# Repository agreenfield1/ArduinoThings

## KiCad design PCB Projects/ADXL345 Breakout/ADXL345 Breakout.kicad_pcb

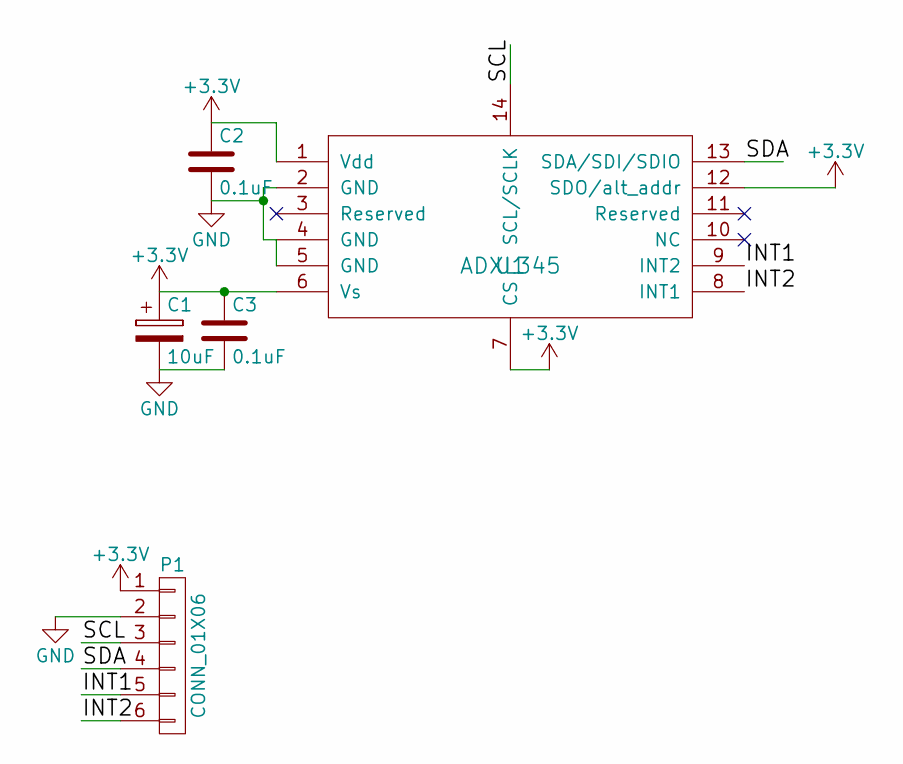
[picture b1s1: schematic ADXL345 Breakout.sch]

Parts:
C1: 10uF; TantalC_SizeA_EIA-3216_HandSoldering
C2, C3: 0.1uF; C_1206_HandSoldering
P1: CONN_01X06; Pin_Header_Straight_1x06
U1: ADXL345; ADXL345-ajggood

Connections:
+3V3: C1.1, C2.1, C3.1, P1.1, U1.1 (Vdd), U1.6 (Vs), U1.7 (CS), U1.12 (SDO/alt_addr)
/INT1: P1.5, U1.9 (INT2)
/INT2: P1.6, U1.8 (INT1)
/SCL: P1.3, U1.14 (SCL/SCLK)
/SDA: P1.4, U1.13 (SDA/SDI/SDIO)
GND: C1.2, C2.2, C3.2, P1.2, U1.2 (GND), U1.4 (GND), U1.5 (GND)

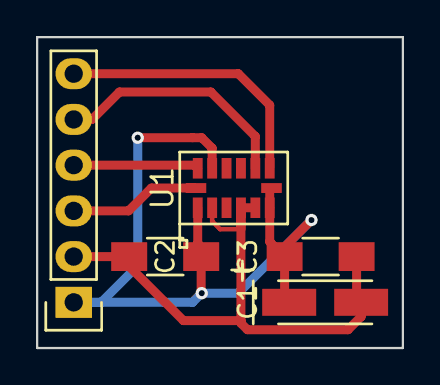
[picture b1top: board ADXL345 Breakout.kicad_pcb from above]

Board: 2 copper layers, 20.3 x 17.3 mm, 5 parts (0 on the bottom side), 6 nets.

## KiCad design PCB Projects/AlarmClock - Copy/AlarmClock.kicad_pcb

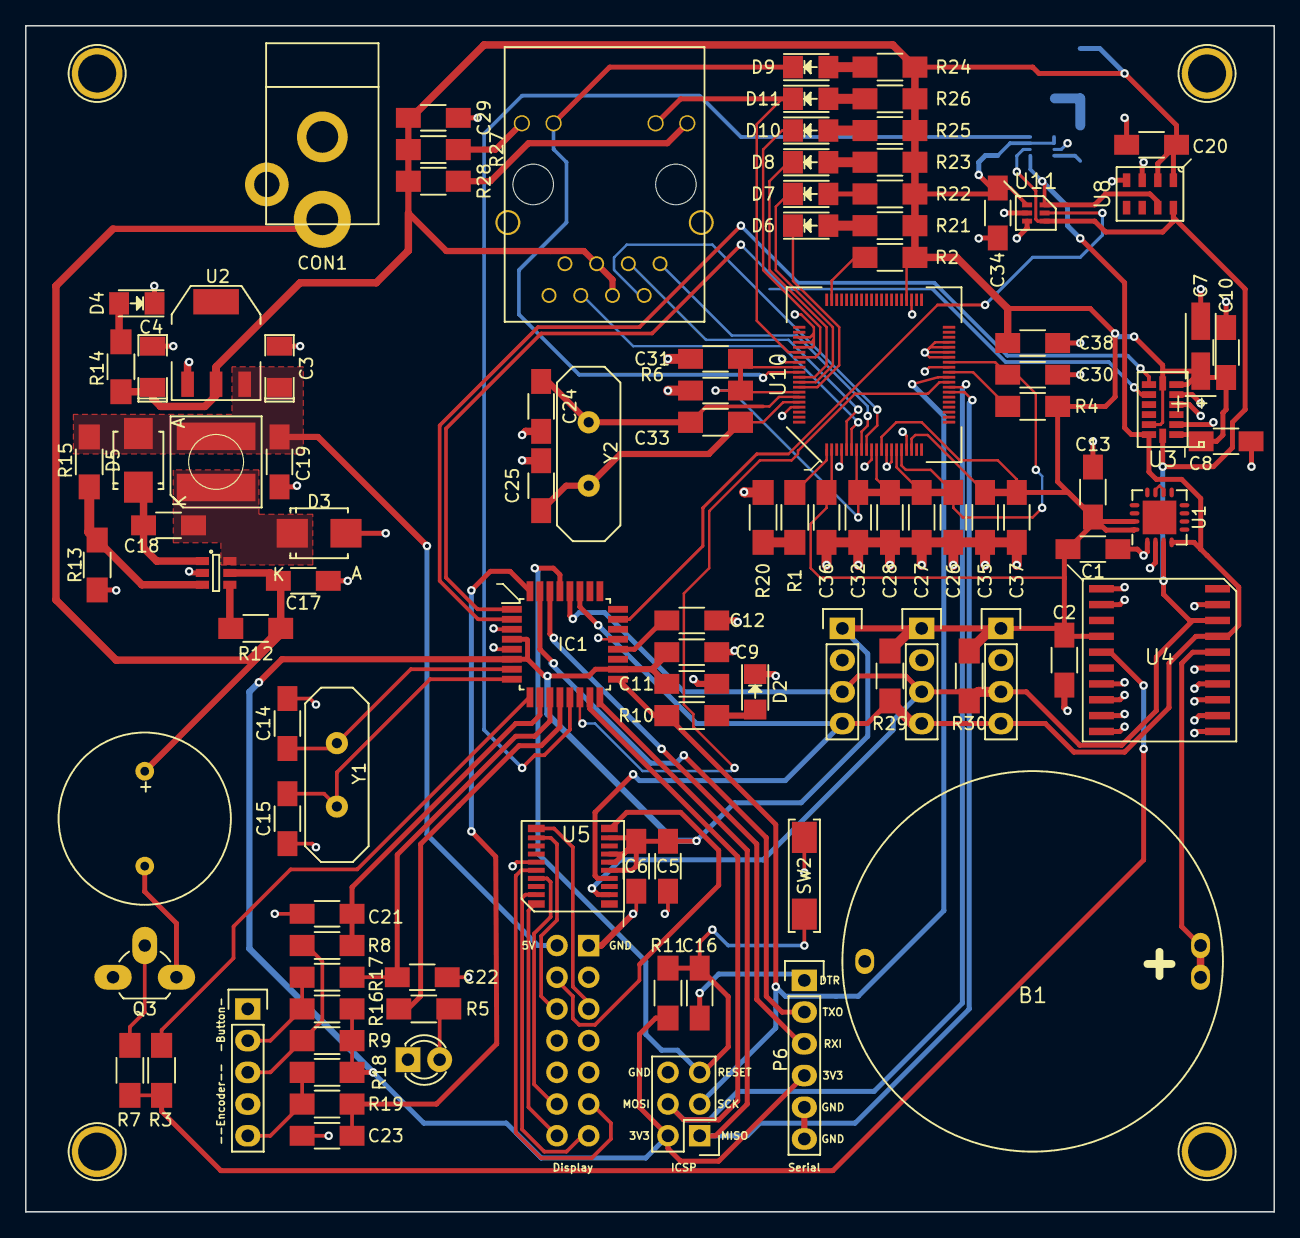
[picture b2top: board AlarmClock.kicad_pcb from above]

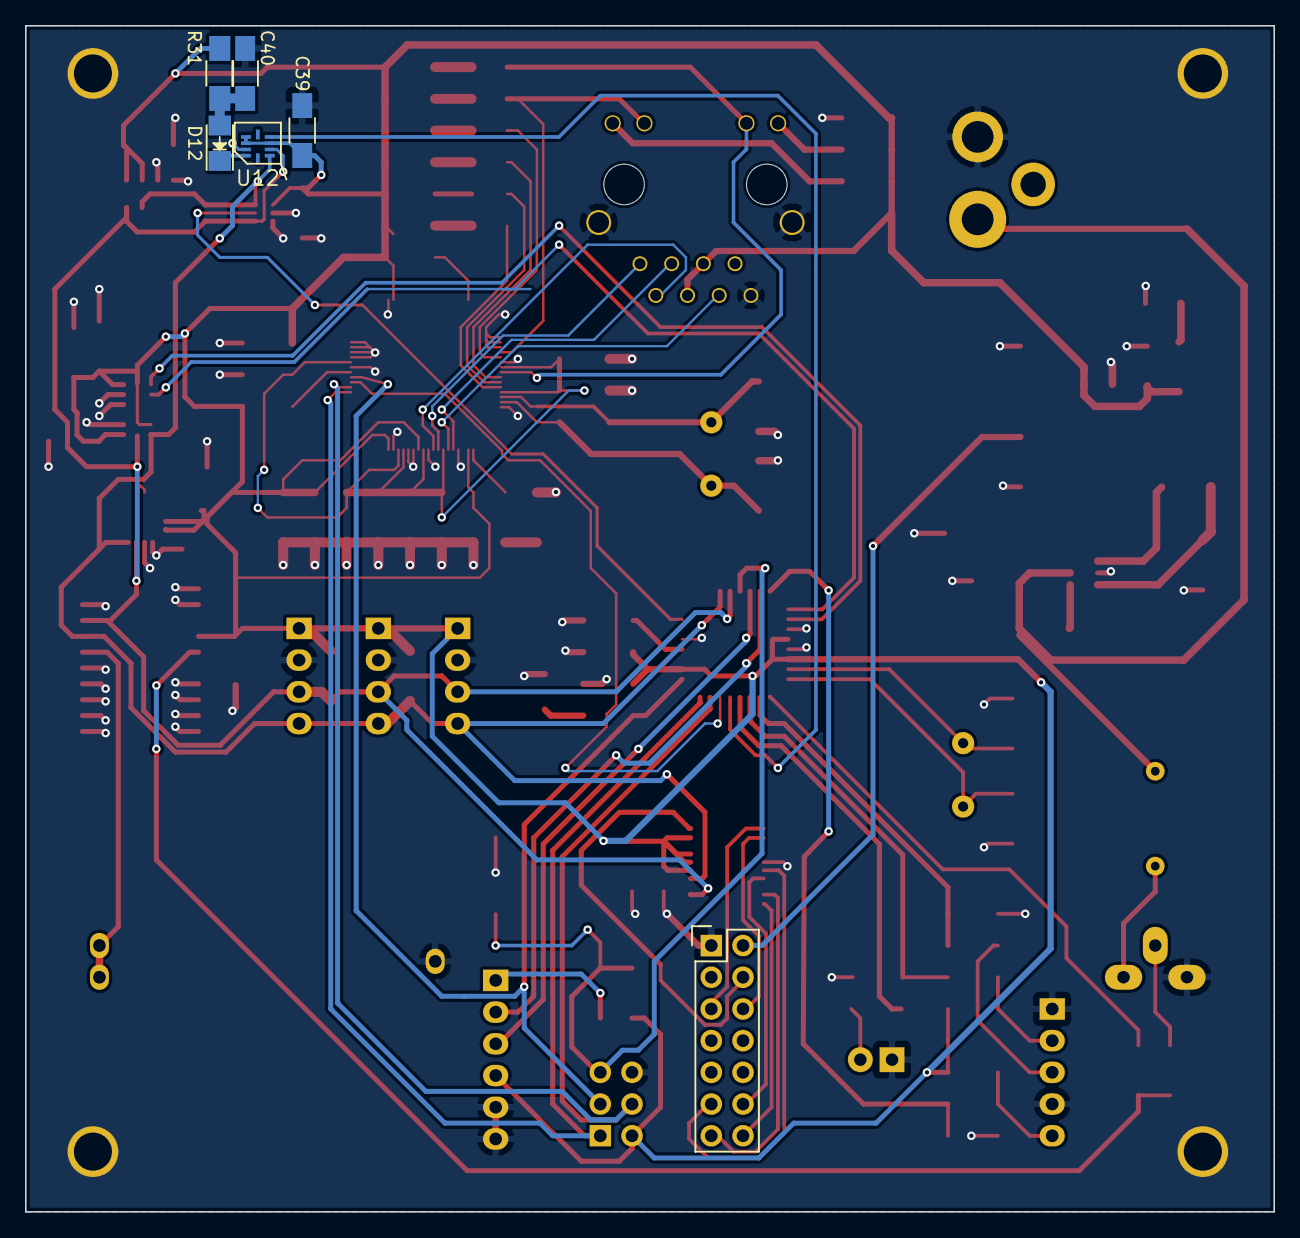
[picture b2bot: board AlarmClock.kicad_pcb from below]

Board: 2 copper layers, 100.0 x 95.0 mm, 110 parts (6 on the bottom side), 75 nets.

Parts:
B1: CR123; CR2032Holder
C1, C13: C_Small; C_1206_HandSoldering
C2: 1uf; C_1206_HandSoldering
C3, C4: 10uf; SMD-1206_Pol
C5: 10uf; C_1206_HandSoldering
C6, C20, C34, C39: 0.1uf; C_1206_HandSoldering
C7: 10uF; TantalC_SizeA_EIA-3216_HandSoldering
C8, C10, C12, C16: 0.1uF; C_1206_HandSoldering
C9, C17: 10UF; C_1206_HandSoldering
C11: 0.1UF; C_1206_HandSoldering
C14, C15: 22p; C_1206_HandSoldering
C18: 22nF; C_1206_HandSoldering
C19: 22uF; C_1206_HandSoldering
C21, C22, C23: 0.01uf; C_1206_HandSoldering
C24, C25: 12pF; C_1206_HandSoldering
C26, C27, C28, C29, C30, C31, C32, C33, C35, C36, C37, C38: 100nF; C_1206_HandSoldering
C40: 15uF; C_1206_HandSoldering
CON1: BARREL_JACK; DC-Jack
D1: LED; LED-3MM
D2, D4: LED; LED_1206
D3: B230A-13-F; SMB_Standard
D5: 1N4148; SMB_Standard
D6, D7, D8, D9, D10, D11, D12: Led_Small; LED_1206
IC1: ATMEGA328P-A; TQFP-32_7x7mm_Pitch0.8mm
J1: HR911105A; HR911105a
L1: INDUCTOR_SMALL; Inductor
P1, P2, P3: CONN_01X04; Pin_Header_Straight_1x04
P4: CONN_02X03; Pin_Header_Straight_2x03
P5: CONN_02X07; Pin_Header_Straight_2x07
P6: CONN_01X06; Pin_Header_Straight_1x06
Q3: Q_NPN_EBC; TO-92_Rugged
R1: 12k; R_1206_HandSoldering
R2, R4, R8, R9, R10, R11, R16, R17, R18, R19: 10k; R_1206_HandSoldering
R3: 1.5k; R_1206_HandSoldering
R5: 220; R_1206_HandSoldering
R6: 1M; R_1206_HandSoldering
R7: 0; R_1206_HandSoldering
R12: 100k; R_1206_HandSoldering
R13: 9.53k; R_1206_HandSoldering
R14, R29, R30: 4.7k; R_1206_HandSoldering
R15: 49.9k; R_1206_HandSoldering
R20: 300; R_1206_HandSoldering
R21, R22, R23, R24, R25, R26, R27, R28: 1k; R_1206_HandSoldering
R31: 30; R_1206_HandSoldering
SW2: SW_PUSH_SMALL; SW_SPST_REED_CT05-XXXX-J1
U1: TSYS01; UQFN-16-1EP_4x4mm_Pitch0.65mm
U2: LD1117S33TR; SOT-223
U3: ADXL345; ADXL345-ajggood
U4: DS3232_RTC; SO20(DS3232)
U5: PCF8574TS/3; SOT266-1
U6: Buzzer; Buzzer(AZ-1440S)
U7: MP2359-BuckReg; SOT-23-6
U8: MS56110; MS56110-QFN
U9: Rotary_Encoder; Pin_Header_Straight_1x05
U10: W5100
U11: TSL2581
U12: Si1145
Y1: Crystal_Small; HC-18UV
Y2: 25MHz; HC-18UV

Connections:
+1V8: C26.1, C27.1, C28.1, C30.1, C31.1, C32.1, C33.1, U10.7, U10.11, U10.15, U10.16, U10.33, U10.69, U10.74
+3V3: C1.1, C2.1, C4.1, C5.2, C6.2, C7.1, C8.1, C9.1, C10.1, C11.1, C13.2, C20.1, C29.1, C34.1, C35.1, C36.1, C37.1, C38.1, C39.1, IC1.4, IC1.6, IC1.18, J1.4, J1.5, P1.1, P2.1, P3.1, P4.2, P6.4, R2.1, R4.1, R9.2, R11.1, R14.1, R16.2, R18.2, R21.2, R22.2, R23.2, R24.2, R25.2, R26.2, R27.2, R28.2, R29.1, R30.1, R31.2, U1.15, U1.16, U2.2, U3.1, U3.6, U3.7, U3.12, U4.4, U5.5, U5.6, U5.7, U5.9, U8.1, U8.2, U10.2, U10.12, U10.18, U10.44, U11.1, U12.3, U12.6, U12.7
+5V: C3.1, C19.1, D5.2, L1.2, P5.2, R15.1, U2.3
+12V: C17.1, CON1.1, R12.1, U6.2, U7.5
+BATT: B1.2, U4.16
/A0: IC1.23, U11.5
/D2: C23.1, IC1.32, R19.2
/D3: IC1.1, U3.9
/D4: IC1.2, U3.8
/D5: IC1.9, R3.1
/D6: C21.1, IC1.10, R8.2
/D7: C22.1, IC1.11, R17.2
/D8: IC1.12, R5.1
/D9: IC1.13, U12.4
/D10: IC1.14, U10.29
/DTR: C16.1, P6.1
/MISO: IC1.16, P4.1, U10.27
/MOSI: IC1.15, P4.4, U10.28
/P0: P5.4, U5.10
/P1: P5.5, U5.11
/P2: P5.6, U5.12
/P4: P5.11, U5.16
/P5: P5.12, U5.17
/P6: P5.13, U5.19
/P7: P5.14, U5.20
/PWM: R3.2, R7.2, U4.5
/RESET: C16.2, IC1.29, P4.5, R11.2, SW2.1
/RXI: IC1.30, P6.3
/SCK: IC1.17, P4.3, R10.1, U10.30
/SCL: IC1.28, P1.3, P2.3, P3.3, R30.2, U1.3, U3.14, U4.18, U5.2, U8.8, U11.4, U12.2
/SDA: IC1.27, P1.4, P2.4, P3.4, R29.2, U1.4, U3.13, U4.17, U5.4, U8.7, U11.6, U12.1
/TXO: IC1.31, P6.2
GND: B1.1, C1.2, C2.2, C3.2, C4.2, C5.1, C6.1, C7.2, C8.2, C9.2, C10.2, C11.2, C12.2, C13.1, C14.1, C15.1, C17.2, C19.2, C20.2, C21.2, C22.2, C23.2, C24.2, C25.2, C26.2, C27.2, C28.2, C29.2, C30.2, C31.2, C32.2, C33.2, C34.2, C35.2, C36.2, C37.2, C38.2, C39.2, C40.2, CON1.2, D1.1, D2.1, D3.2, D4.1, IC1.3, IC1.5, IC1.21, J1.8, J1.13, J1.14, P1.2, P2.2, P3.2, P4.6, P5.1, P6.5, P6.6, Q3.1, R13.2, R20.1, SW2.2, U1.1, U1.2, U2.1, U3.2, U3.4, U3.5, U4.1, U4.2, U4.7, U4.8, U4.9, U4.10, U4.11, U4.12, U4.13, U4.14, U4.15, U4.19, U5.15, U7.2, U8.3, U8.4, U9.1, U9.4, U10.4, U10.10, U10.13, U10.14, U10.17, U10.32, U10.34, U10.35, U10.36, U10.37, U10.43, U10.63, U10.64, U10.65, U10.68, U10.77, U11.2, U11.3, U12.8
unnamed: C12.1, IC1.20
unnamed: C14.2, IC1.7, Y1.1
unnamed: C15.2, IC1.8, Y1.2
unnamed: C18.1, D5.1, U7.1
unnamed: C18.2, D3.1, L1.1, U7.6
unnamed: C24.1, R6.1, U10.75, Y2.1
unnamed: C25.1, R6.2, U10.76, Y2.2
unnamed: C40.1, D12.2, R31.1
unnamed: D1.2, R5.2
unnamed: D2.2, R10.2
unnamed: D4.2, R14.2
unnamed: D6.1, U10.73
unnamed: D6.2, R21.1
unnamed: D7.1, U10.72
unnamed: D7.2, R22.1
unnamed: D8.1, U10.71
unnamed: D8.2, R23.1
unnamed: D9.1, J1.11, U10.70
unnamed: D9.2, R24.1
unnamed: D10.1, U10.67
unnamed: D10.2, R25.1
unnamed: D11.1, J1.10, U10.66
unnamed: D11.2, R26.1
unnamed: D12.1, U12.9
unnamed: J1.1, U10.8
unnamed: J1.2, U10.9
unnamed: J1.3, U10.5
unnamed: J1.6, U10.6
unnamed: J1.9, R28.1
unnamed: J1.12, R27.1
unnamed: Q3.2, R7.1
unnamed: Q3.3, U6.1
unnamed: R1.1, R20.2
unnamed: R1.2, U10.1
unnamed: R2.2, U10.59
unnamed: R4.2, U10.31
unnamed: R8.1, R9.1, U9.3
unnamed: R12.2, U7.4
unnamed: R13.1, R15.2, U7.3
unnamed: R16.1, R17.1, U9.2
unnamed: R18.1, R19.1, U9.5
unnamed: U1.10, U1.11

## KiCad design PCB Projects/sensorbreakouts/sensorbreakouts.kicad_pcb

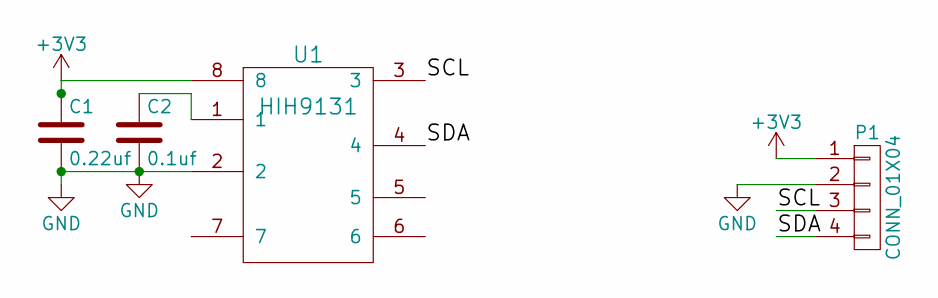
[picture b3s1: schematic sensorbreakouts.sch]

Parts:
C1: 0.22uf; C_1206_HandSoldering
C2: 0.1uf; C_1206_HandSoldering
P1: CONN_01X04; Pin_Header_Straight_1x04
U1: HIH9131; SOIC-8_3.9x4.9mm_Pitch1.27mm

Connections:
+3V3: C1.1, P1.1, U1.8
/SCL: P1.3, U1.3
/SDA: P1.4, U1.4
GND: C1.2, C2.2, P1.2, U1.2
unnamed: C2.1, U1.1

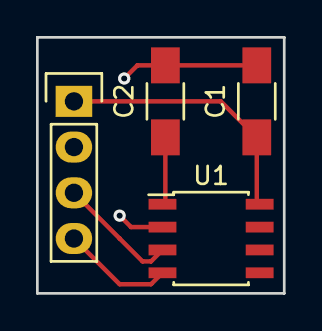
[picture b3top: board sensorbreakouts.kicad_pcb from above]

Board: 2 copper layers, 13.7 x 14.2 mm, 4 parts (0 on the bottom side), 5 nets.
